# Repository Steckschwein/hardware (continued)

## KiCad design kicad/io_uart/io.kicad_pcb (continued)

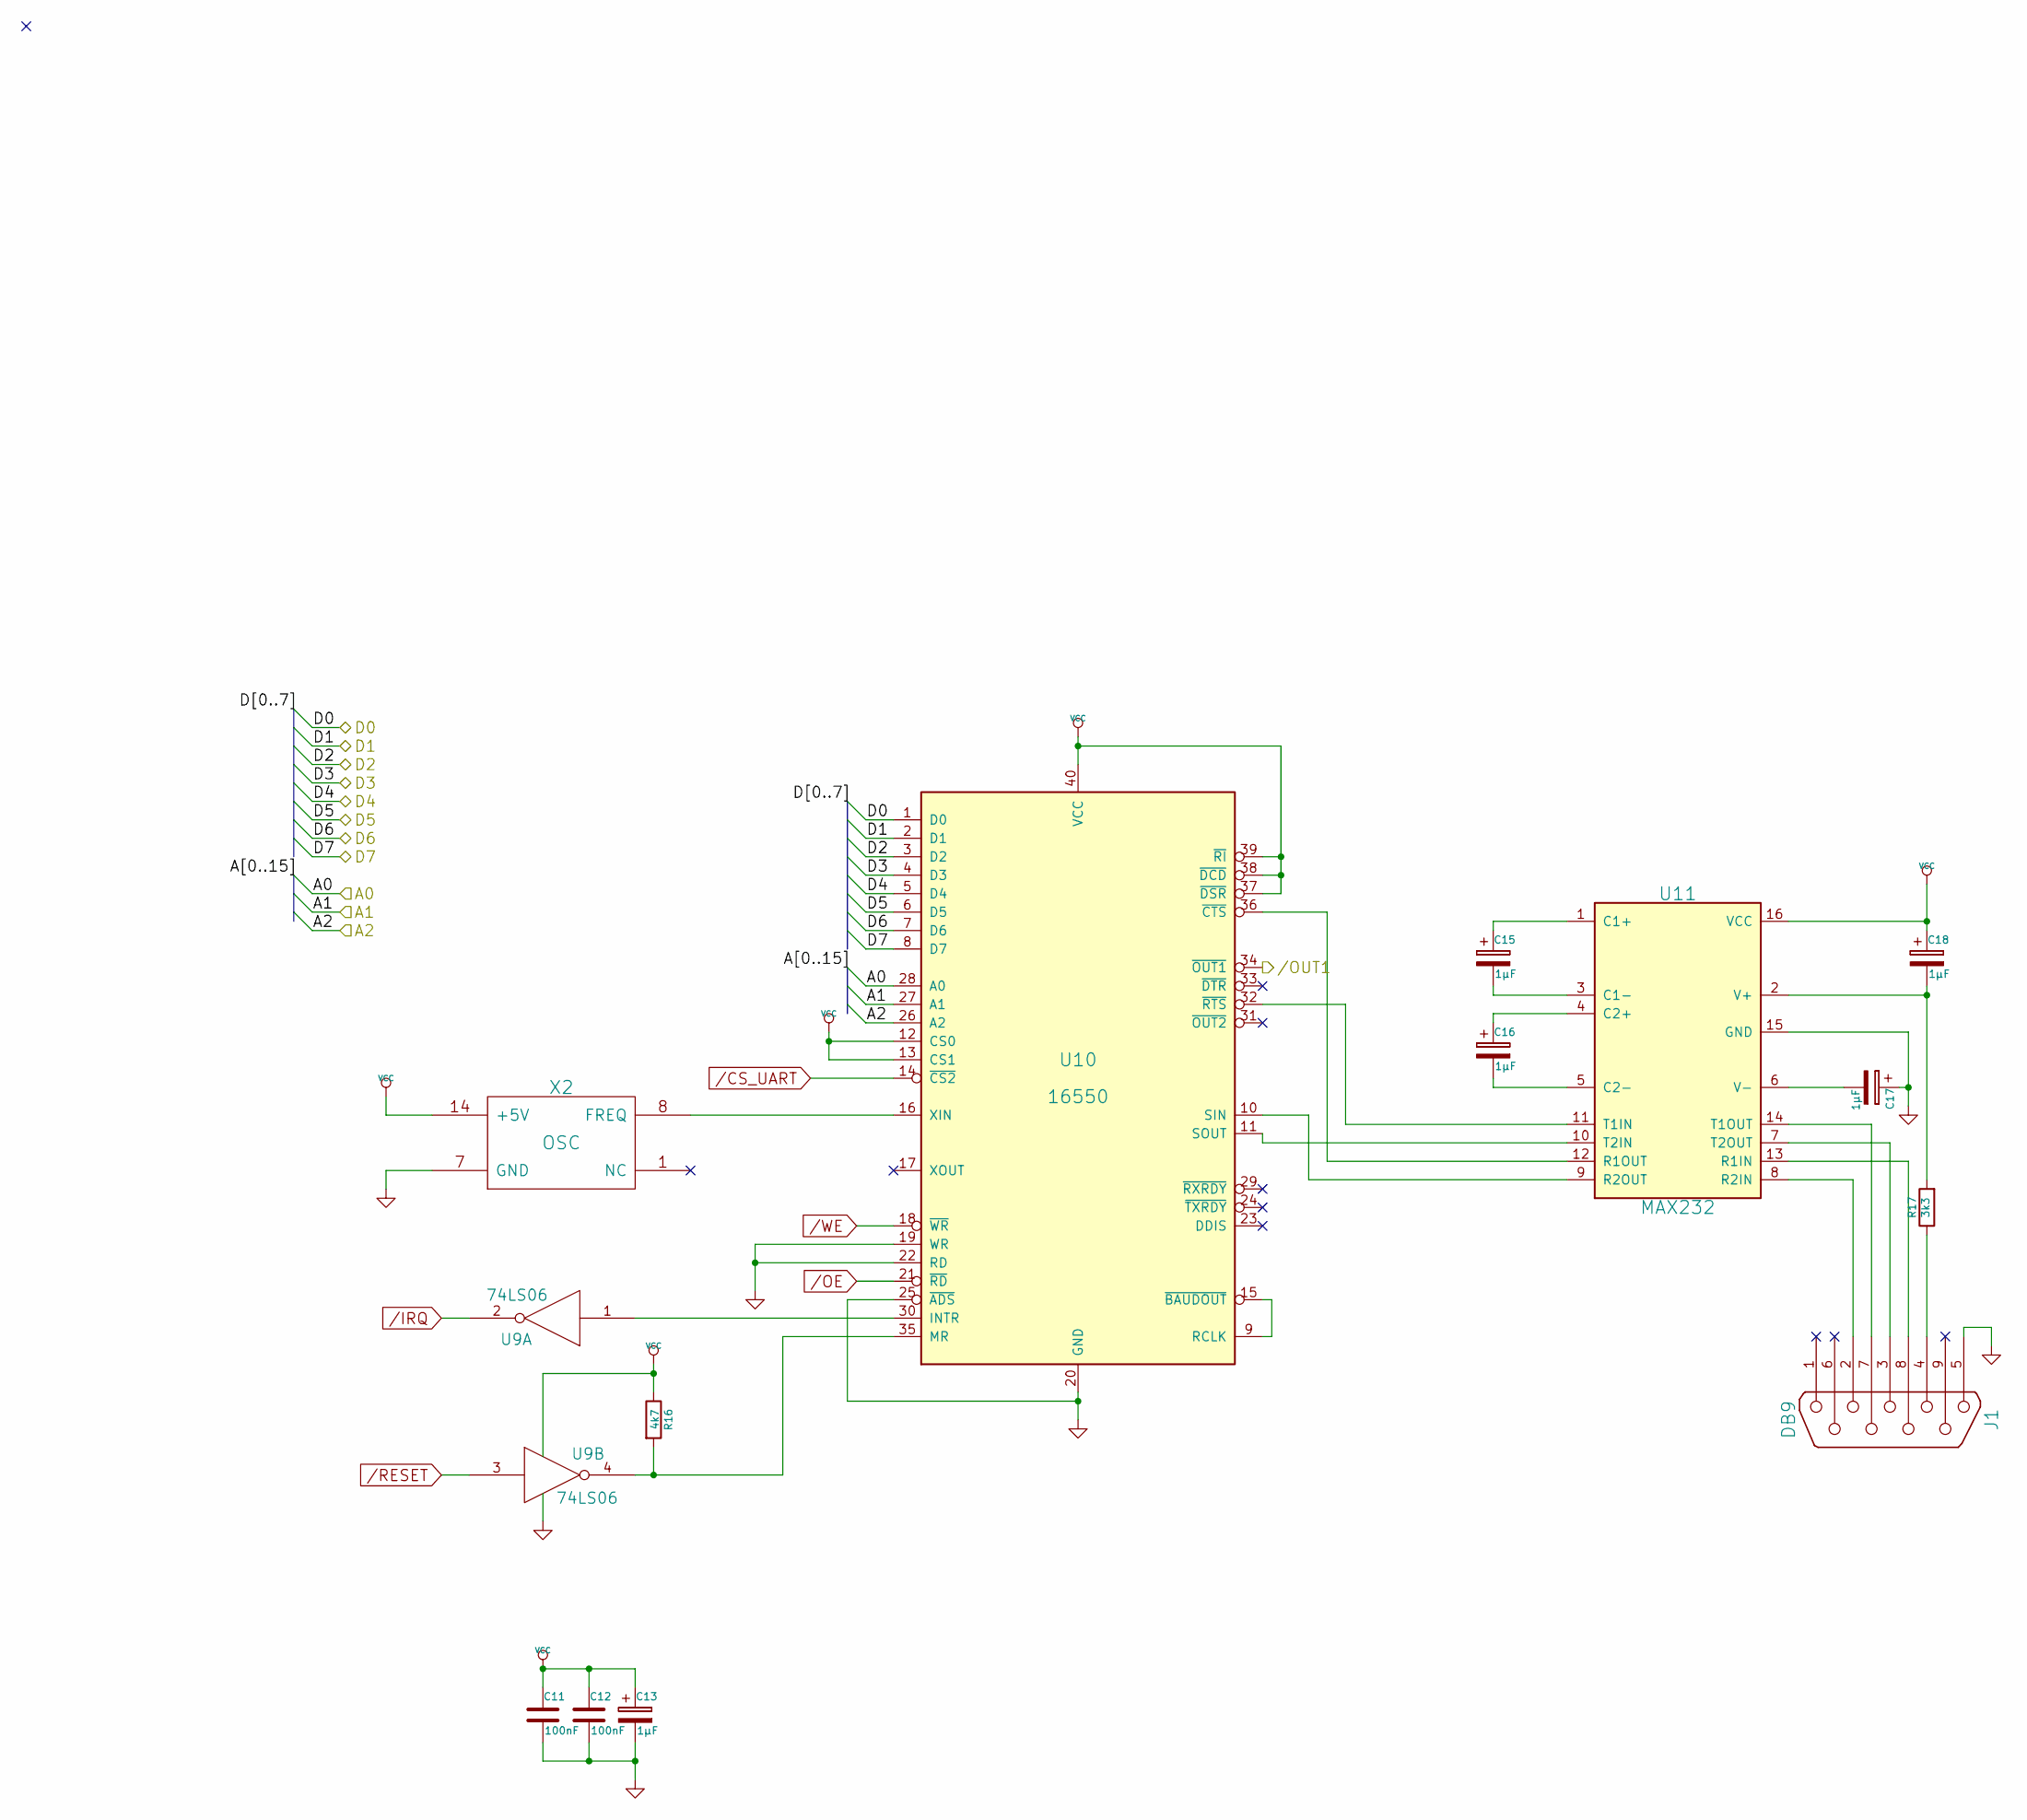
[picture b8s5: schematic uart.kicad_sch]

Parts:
C11, C12: 100nF; C_Rect_L4_W2.5_P2.5
C13, C15, C16, C17, C18: 1µF; C_Radial_D5_L6_P2.5
J1: DB9; DB9MC
R16: 4k7; Resistor_Horizontal_RM7mm
R17: 3k3; Resistor_Horizontal_RM7mm
U9: 74LS06; DIP-14_W7.62mm_LongPads
U10: 16550; DIP-40_W15.24mm_LongPads
U11: MAX232; DIP-16_W7.62mm_LongPads
X2: OSC; KXO-200_LargePads

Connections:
/CS_UART: U10.14 (~CS2); also elsewhere on the board
/Connector/A0: U10.28 (A0); also elsewhere on the board
/Connector/A1: U10.27 (A1); also elsewhere on the board
/Connector/A2: U10.26 (A2); also elsewhere on the board
/Connector/D0: U10.1 (D0); also elsewhere on the board
/Connector/D1: U10.2 (D1); also elsewhere on the board
/Connector/D2: U10.3 (D2); also elsewhere on the board
/Connector/D3: U10.4 (D3); also elsewhere on the board
/Connector/D4: U10.5 (D4); also elsewhere on the board
/Connector/D5: U10.6 (D5); also elsewhere on the board
/Connector/D6: U10.7 (D6); also elsewhere on the board
/Connector/D7: U10.8 (D7); also elsewhere on the board
/IRQ: U9.2; also elsewhere on the board
/Joystick Ports//JOYPORT_ENABLE: U10.34 (~OUT1); also elsewhere on the board
/OE: U10.21 (~RD); also elsewhere on the board
/RESET: U9.3; also elsewhere on the board
/WE: U10.18 (~WR); also elsewhere on the board
GND: C11.2, C12.2, C13.2, C17.1, J1.5, U9.7 (GND), U10.19 (WR), U10.20 (GND), U10.22 (RD), U10.25 (~ADS), U11.15 (GND), X2.7 (GND); also elsewhere on the board
unnamed: C15.1, U11.1 (C1+)
unnamed: C15.2, U11.3 (C1-)
unnamed: C16.1, U11.4 (C2+)
unnamed: C16.2, U11.5 (C2-)
unnamed: C17.2, U11.6 (V-)
unnamed: C18.2, R17.2, U11.2 (V+)
unnamed: J1.2, U11.8 (R2IN)
unnamed: J1.3, U11.7 (T2OUT)
unnamed: J1.4, R17.1
unnamed: J1.7, U11.14 (T1OUT)
unnamed: J1.8, U11.13 (R1IN)
unnamed: R16.2, U9.4, U10.35 (MR)
unnamed: U10.10 (SIN), U11.9 (R2OUT)
unnamed: U10.11 (SOUT), U11.10 (T2IN)
unnamed: U10.9 (RCLK), U10.15 (~BAUDOUT)
unnamed: U10.16 (XIN), X2.8 (FREQ)
unnamed: U9.1, U10.30 (INTR)
unnamed: U10.32 (~RTS), U11.11 (T1IN)
unnamed: U10.36 (~CTS), U11.12 (R1OUT)
VCC: C11.1, C12.1, C13.1, C18.1, R16.1, U9.14 (VCC), U10.12 (CS0), U10.13 (CS1), U10.37 (~DSR), U10.38 (~DCD), U10.39 (~RI), U10.40 (VCC), U11.16 (VCC), X2.14 (+5V); also elsewhere on the board

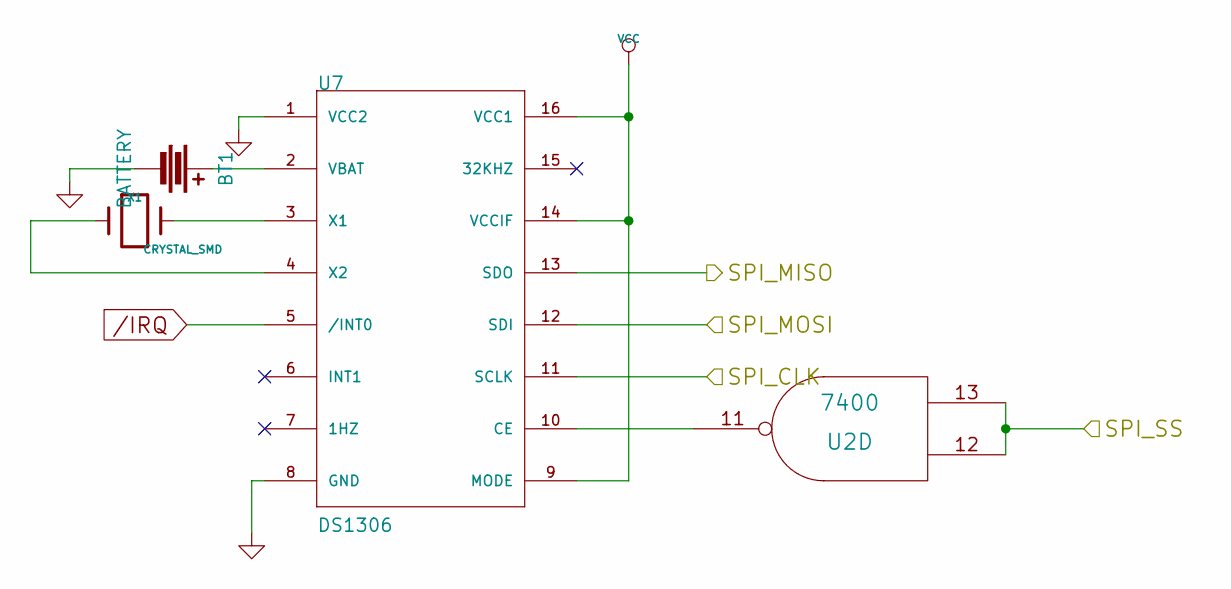
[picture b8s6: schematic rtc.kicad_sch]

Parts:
BT1: BATTERY; CR2032H
U2: 7400; DIP-14_W7.62mm_LongPads
U7: DS1306; DIP-16_W7.62mm_LongPads
X1: CRYSTAL_SMD; Crystal_Round_Vertical_3mm_BigPad

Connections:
/IRQ: U7.5 (/INT0); also elsewhere on the board
/PS/2 Controller/SPI_CLK: U7.11 (SCLK); also elsewhere on the board
/PS/2 Controller/SPI_MISO: U7.13 (SDO); also elsewhere on the board
/PS/2 Controller/SPI_MOSI: U7.12 (SDI); also elsewhere on the board
/RTC/SPI_SS: U2.12, U2.13; also elsewhere on the board
GND: BT1.2, U2.7 (GND), U7.1 (VCC2), U7.8 (GND); also elsewhere on the board
unnamed: BT1.1, U7.2 (VBAT)
unnamed: U2.11, U7.10 (CE)
unnamed: U7.3 (X1), X1.2
unnamed: U7.4 (X2), X1.1
VCC: U2.14 (VCC), U7.9 (MODE), U7.14 (VCCIF), U7.16 (VCC1); also elsewhere on the board

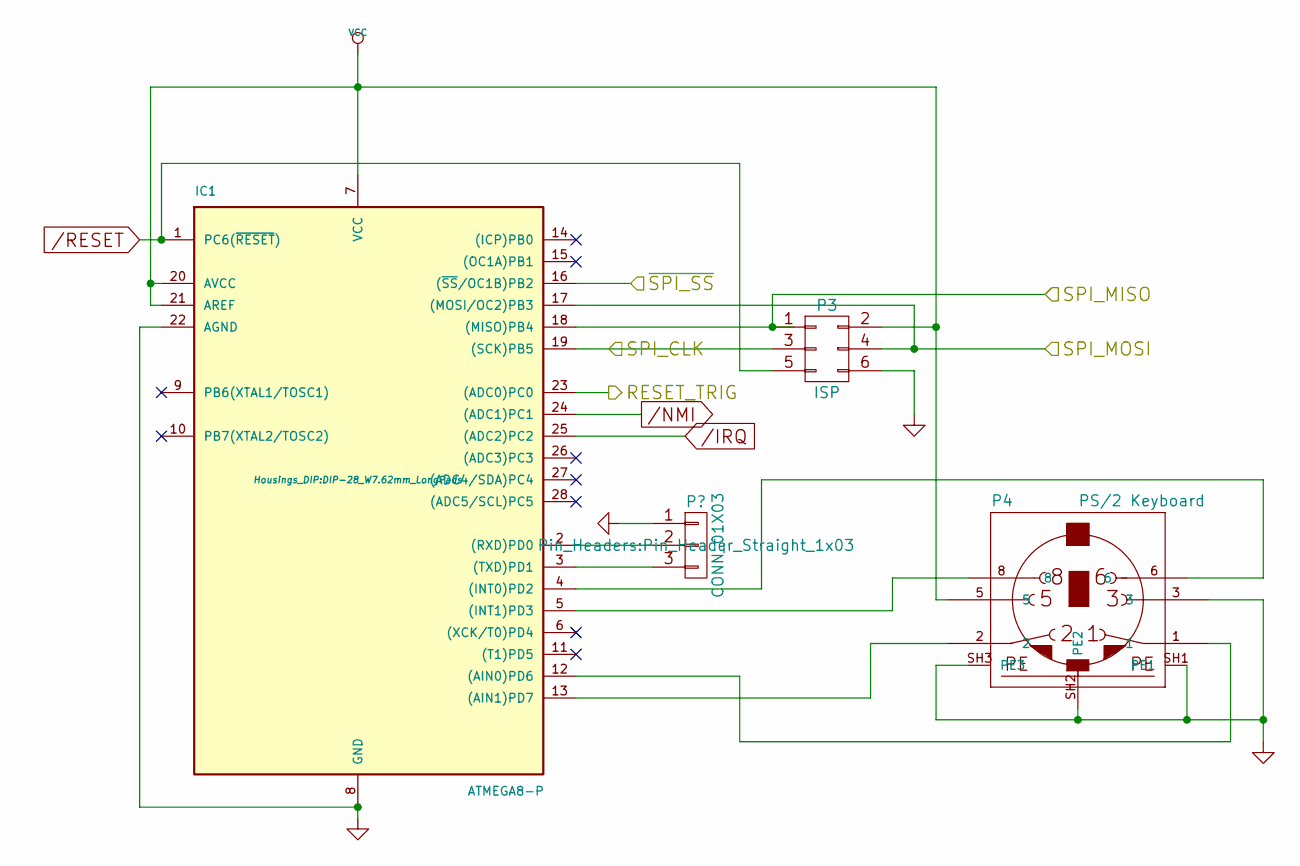
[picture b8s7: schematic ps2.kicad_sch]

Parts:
IC1: ATMEGA8-P; DIP-28_W7.62mm_LongPads
P3: ISP; Pin_Header_Angled_2x03
P4: PS/2 Keyboard; mini_din-M_DIN6

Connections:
/Connector/RESET_TRIG: IC1.23 ((ADC0)PC0); also elsewhere on the board
/IRQ: IC1.25 ((ADC2)PC2); also elsewhere on the board
/NMI: IC1.24 ((ADC1)PC1); also elsewhere on the board
/PS/2 Controller/SPI_CLK: IC1.19 ((SCK)PB5), P3.3; also elsewhere on the board
/PS/2 Controller/SPI_MISO: IC1.18 ((MISO)PB4), P3.1; also elsewhere on the board
/PS/2 Controller/SPI_MOSI: IC1.17 ((MOSI/OC2)PB3), P3.4; also elsewhere on the board
/PS/2 Controller/~SPI_SS: IC1.16 ((~SS/OC1B)PB2); also elsewhere on the board
/RESET: IC1.1 (PC6(~RESET)), P3.5; also elsewhere on the board
GND: IC1.8 (GND), IC1.22 (AGND), P3.6, P4.3, P4.SH1 (PE1), P4.SH2 (PE2), P4.SH3 (PE3); also elsewhere on the board
unnamed 56: IC1.2 ((RXD)PD0); also elsewhere on the board
unnamed 57: IC1.3 ((TXD)PD1); also elsewhere on the board
unnamed: IC1.4 ((INT0)PD2), P4.6
unnamed: IC1.5 ((INT1)PD3), P4.8
unnamed: IC1.12 ((AIN0)PD6), P4.1
unnamed: IC1.13 ((AIN1)PD7), P4.2
VCC: IC1.7 (VCC), IC1.20 (AVCC), IC1.21 (AREF), P3.2, P4.5; also elsewhere on the board

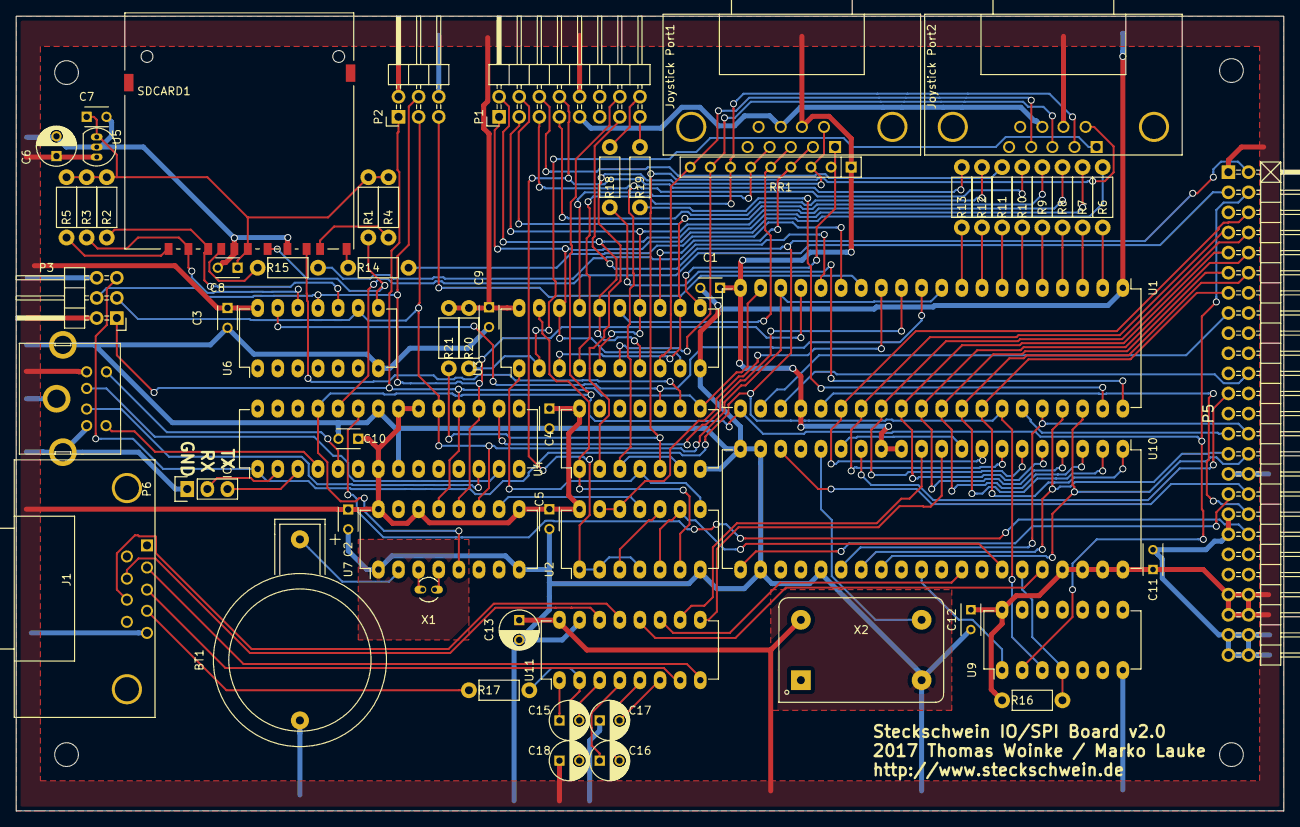
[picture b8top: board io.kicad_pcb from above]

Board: 2 copper layers, 160.0 x 100.3 mm, 67 parts (0 on the bottom side), 105 nets.

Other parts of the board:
Joystick Port1, Joystick Port2: DB9; DB9MC
MH1, MH2, MH3, MH4: MountingHole_3mm_RevA_Date21Jun2010; MountingHole_3mm
P6: CONN_01X03; Pin_Header_Straight_1x03
SDCARD1: SD_Card; SD_Card_Receptacle

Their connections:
/SD Card/SD_CARD_DETECT: SDCARD1.10; also elsewhere on the board
/SD Card/SD_WRITE_PROTECT: SDCARD1.11; also elsewhere on the board
GND: Joystick Port1.8, Joystick Port2.8, P6.1, SDCARD1.3, SDCARD1.6; also elsewhere on the board
unnamed 49: SDCARD1.4; also elsewhere on the board
unnamed 56: P6.2; also elsewhere on the board
unnamed 57: P6.3; also elsewhere on the board
unnamed 89: Joystick Port1.1; also elsewhere on the board
unnamed 90: Joystick Port1.2; also elsewhere on the board
unnamed 91: Joystick Port1.3; also elsewhere on the board
unnamed 92: Joystick Port1.4; also elsewhere on the board
unnamed 94: Joystick Port1.6; also elsewhere on the board
unnamed 96: Joystick Port2.1; also elsewhere on the board
unnamed 97: Joystick Port2.2; also elsewhere on the board
unnamed 98: Joystick Port2.3; also elsewhere on the board
unnamed 99: Joystick Port2.4; also elsewhere on the board
unnamed 101: Joystick Port2.6; also elsewhere on the board
unnamed 103: SDCARD1.5; also elsewhere on the board
unnamed 104: SDCARD1.2; also elsewhere on the board
unnamed 105: SDCARD1.1; also elsewhere on the board
unnamed 106: SDCARD1.8; also elsewhere on the board
unnamed 107: SDCARD1.9; also elsewhere on the board
unnamed 121: SDCARD1.7; also elsewhere on the board
VCC: Joystick Port1.7, Joystick Port2.7; also elsewhere on the board

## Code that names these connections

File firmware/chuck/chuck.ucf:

NET CPU_d<7>      LOC = P62;
NET CPU_d<6>      LOC = P63;
NET CPU_d<5>      LOC = P61;
NET CPU_d<4>      LOC = P58;
NET CPU_d<3>      LOC = P57;
NET CPU_d<2>      LOC = P56;
NET CPU_d<1>      LOC = P55;
NET CPU_d<0>      LOC = P54;
#
NET CPU_a<0>      LOC = P65;
NET CPU_a<1>      LOC = P66;
#
NET CPU_a<4>      LOC = P67;
NET CPU_a<5>      LOC = P68;
NET CPU_a<6>      LOC = P69;
NET CPU_a<7>      LOC = P70;
NET CPU_a<8>      LOC = P71;
NET CPU_a<9>      LOC = P72;
NET CPU_a<10>     LOC = P75;
NET CPU_a<11>     LOC = P76;
NET CPU_a<12>     LOC = P77;
NET CPU_a<13>     LOC = P79;
NET CPU_a<14>     LOC = P80;
NET CPU_a<15>     LOC = P81;
#
NET EXT_a<14>     LOC = P82;
NET EXT_a<15>     LOC = P83;
NET EXT_a<16>     LOC = P84;
NET EXT_a<17>     LOC = P1;
NET EXT_a<18>     LOC = P2;
#
NET CS_OPL   	  LOC = P53;
NET CS_VIA        LOC = P51;
NET CS_SLOT1      LOC = P50;
NET CS_SLOT0      LOC = P39;
NET CSR_VDP       LOC = P47;
NET CSW_VDP       LOC = P25;
NET CS_UART       LOC = P48;
NET CS_ROM        LOC = P4;
NET CS_RAM        LOC = P5;
NET CS_BUFFER     LOC = P52;
#
#
NET CPU_rw    	  LOC = P44; 
NET OE        	  LOC = P6; 
NET WE    	  LOC = P7; 
# NET W		  LOC = P11;
# NET R		  LOC = P26;
NET CPU_phi2      LOC = P3; 
#
NET CPU_rdy       LOC = P40;
NET VDP_wait      LOC = P45;
#
NET CLKIN         LOC = P9; # -- global clock: Pin 9,10,12###
NET RESET         LOC = P74; # -- global reset: Pin 74

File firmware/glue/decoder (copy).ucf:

#PACE: Start of Constraints generated by PACE

#PACE: Start of PACE I/O Pin Assignments
NET "A<0>"  LOC = "P8"  ;
NET "A<10>"  LOC = "P24"  ;
NET "A<11>"  LOC = "P25"  ;
NET "A<1>"  LOC = "P9"  ;
NET "A<2>"  LOC = "P11"  ;
NET "A<3>"  LOC = "P12"  ;
NET "A<4>"  LOC = "P13"  ;
NET "A<5>"  LOC = "P14"  ;
NET "A<6>"  LOC = "P18"  ;
NET "A<7>"  LOC = "P19"  ;
NET "A<8>"  LOC = "P20"  ;
NET "A<9>"  LOC = "P22"  ;
NET "CS_HIRAM"  LOC = "P35"  ;
NET "CS_IO"  LOC = "P44"  ;
NET "CS_LORAM"  LOC = "P34"  ;
NET "CS_ROM"  LOC = "P33"  ;
NET "CS_UART"  LOC = "P36"  ;
NET "CS_VDP"  LOC = "P38"  ;
NET "CS_VIA"  LOC = "P37"  ;
NET "MEMCTL"  LOC = "P43"  ;
NET "PHI2"  LOC = "P5"  ;
NET "RD"  LOC = "P27"  ;
NET "RDY"  LOC = "P29"  ;
NET "ROMOFF"  LOC = "P1"  ;
NET "RW"  LOC = "P26"  ;
NET "WR"  LOC = "P28"  ;

#PACE: Start of PACE Area Constraints

#PACE: Start of PACE Prohibit Constraints

#PACE: End of Constraints generated by PACE

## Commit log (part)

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2019-03-11 add serial debug
2019-03-11 enable spi slave
2019-03-11 optimized scancode decoding
2019-03-13 cleanup
2019-03-13 cleanup fillers
2019-03-13 enable serial debug via define
2019-03-26 serial headers
2019-03-30 skkdfnskj
2019-04-07 send mode (unusable, bug ridden, incomplete, still sends crap)
2019-04-07 still buggy
2019-04-07 still broken
2019-04-07 k,hdc
2019-04-10 remove avrdude device specifics, dependency fix
2019-05-01 decoder/wsgen/clock cpld vhdl sources
2019-05-04 tests, asserts and fixes
2019-05-04 full address decoder test broken for no apparent reason
2019-05-04 new project, test, fixes
2019-05-04 vhd files back
2019-05-05 reset line, test waveform config
2019-05-05 impact project file
2019-05-08 rdy generation, clock generation PHI2 = CLKIN /2 (saves space)
2019-05-14 fixes
2019-05-27 C16 value
2019-06-12 cpu_mem_rdy.csv cleanup, suppliers
2019-06-12 suggest different rams
2019-07-04 README created online with Bitbucket
2019-07-28 plcc84, full address bus, latch
2019-07-29 removed freq divider
2019-07-29 very cheap cs_ram solution
2019-07-29 almost
2019-07-30 cs_ram cheap solution, rev. 2
2019-08-03 register writes use cs_IOnn lines for debug output
2019-08-03 fix cs_ram, test register write to romoff
2019-08-03 register writes, a13/a14 mapping for rom accesses code reorg removed cs_io03
2019-08-03 cpu pins: vp, sync, be
2019-08-05 pin names, irq and nmi lines
2020-05-30 new address decoder inital
2020-05-31 fixes, testbench
2020-09-27 +keboard, send commands
2020-09-27 +update
2020-09-28 +send keyboard codes
2020-09-29 +keyboard util
2020-09-29 +merge
2020-09-29 +fix makefile
2020-09-29 +fix caps lock / shift
2020-09-29 +recv. keyboard commands
2020-10-03 +kbd status support +improved cmd handling
2020-10-04 fix shift key
2020-10-04 if proper formatted
2020-10-05 assert IRQ when byte in buffer, release when byte reansferred via spi
2020-10-05 +cmd timeout +doc
2020-10-07 +status check
2020-10-10 +echo watchdog +fix timing on identify
2020-10-11 pull irq line when buffer >0 bytes, release irq when buffer empty
2020-11-09 use IRQ by default
2020-11-14 +reset and init sequence +clean code
2020-11-19 removed xilinx projects
2020-12-31 +revision keyboard firmware and host irq handling
2021-01-03 +kbd cmd engine +bios init sequence
2021-05-27 cpu_mem_cpld initial
2021-08-22 gitignore file
2021-08-29 io components
2022-03-03 cpld version with uart
2022-03-03 libs
2022-03-03 remove all global labels
2022-04-24 initial
2022-04-24 add more stuff
2022-04-24 nope
2022-04-24 remove csw_vdp, csr_vdp. add cs_vdp_
2022-04-24 removed csr_vdp, csw_vdp. cs_vdp only
2022-04-24 pinout rearranged for better fitting
2022-04-24 csw_vdp, csr_vdp replaced by cs_vdp, cleanup
2022-04-24 more tests
2022-04-26 use fitter generated pinout
2022-05-16 cpu cpld 512
2022-05-18 add cs_uart2, remove a2,a3
2022-05-18 added cs_uart2, /WE for EEPROM
2022-05-18 uart2 pin assignment
2022-05-18 extra capacitor, revision text
2022-05-18 eeprom rw jumper
2022-05-20 new routing attempt
2022-05-22 cleanup autorouted traces
2022-05-22 zones refilled
2022-05-22 gerber files
2022-05-25 swap uart and uart2
2022-08-25 rdygen disabled
2022-09-04 data bus interface back on
2022-09-10 test with hardcoded cs_rom and cs_ram
2022-09-20 rdwr process
2022-09-23 +ROM read ok
2022-09-24 +with uart
2022-09-26 io select term long form
2022-09-26 uart2 cs decoding long form
2022-09-26 reg_select decoding long form
2022-09-26 +concurrent mode
2022-09-26 cs terms longform
2022-09-29 +clean code
2022-09-29 +bitmask conditionals
2022-10-01 +bios ram,rom,uart OK +clean code
2022-10-02 +xmodem cpld bios +clean vhdl
2022-10-03 +static ctrl port read
2022-10-03 +register read
2022-10-04 +init and reg read ok
2022-10-04 +ascii out
2022-10-04 +reg write nearly
2022-10-04 +reg read/write OK :)
2022-10-04 +ext ram +memtest
2022-10-05 +improved memtest
2022-10-05 fix missing cs vdp
2022-10-05 +wait states on cs_rom +revision bank test
2022-10-05 +tristate rdy by default
2022-10-05 +revision rdy, 8Mhz ok
2022-10-07 +clean
2022-10-08 +fix rdy timing +add vdp, opl cs
2022-10-08 +16Mhz ok
2022-10-09 +bios, kernel, timing
2022-10-20 cs_buffer (U10)
2022-10-20 cs buffer to pin 62
2022-10-21 pin 75 even better
2022-10-21 cs line for data bus buffer
2022-10-21 removed sbc
2023-01-15 sbc core
2023-02-06 fix cs_buffer generation
2023-02-11 +memcheck ram/rom bios
2023-02-26 audio video stuff, new placement
2023-03-01 ref #52 +revision, clean code +disable keyboard irq
2023-03-22 pinout for sbc, removed UART2 CS
2023-03-22 cs slot0/slot1
2023-03-22 pinout adjustments
2023-03-22 cpld pinout
2023-03-22 more vias to gnd
2023-03-28 din connector footprints
2023-03-28 complete schematics
2023-03-29 io area relayout
2023-04-01 pinout expansion slot
2023-04-01 added CSR_VDP, CSW_VDP, W, R
2023-04-01 removed U17
2023-04-01 io area placement
2023-04-03 fix ERC messages
2023-04-04 cleanup ERC warnings and errors
2023-04-04 erc cleanup
2023-04-07 routing
2023-04-07 more routing
2023-04-07 routing..
2023-04-10 DRC hell
2023-04-11 DRC hell II
2023-04-11 vdp xtal capacitor footprints THT
2023-04-11 fix CS_OPL, fix DRC warnings
2023-04-11 DRC warnings
2023-04-12 added magic irq diode for W65c22S
2023-04-12 regular sd socket separate masses for analog and digital cleanup routing
2023-04-12 swap pins d6 d7
2023-04-12 created gerber files
2023-04-30 fix mixup of vcc and gnd at the 74244
2023-04-30 fix mixup of vcc and gnd on U29
2023-04-30 fix ISE latch warnings
2023-05-02 backups exclude
2023-05-02 moved .gitignore to kicad/
2023-05-07 filter
2023-05-10 connect cpu_r/W to CPLD
2023-05-10 fix CS_OPL pin mixup
2023-05-10 fix cpu_r/w connection to CPLD
2023-05-11 added R and W, cleanup
2023-05-14 fix dimensions
2023-05-14 fix some ugly routin
2023-05-17 new ps/2 mini din footprint
2023-05-17 better s-video jack footprint
2023-05-24 resistor footprints
2023-06-01 dip 28 footprint
2023-06-05 fix DRC warnings
2023-06-17 +rollback d_out - tbd.
2023-06-19 moved all symbols into custom library
2023-06-20 moved all footprints into local library
2023-06-20 removed all other project libraries
2023-07-01 generate phi2 from master clock via counter TEST: gate cs_uart, csw_vdp, csr_vdp via PHI2
2023-07-02 fix spi selects
2023-07-02 fix sd card socket symbol
2023-07-02 assigned footprint
2023-07-02 cosmetics
2023-07-02 sd card detect back
2023-07-02 fix drc error
2023-07-02 sd card detect routed, cosmetics
2023-07-02 sd card pullup resistor pack
2023-07-02 revision text
2023-07-02 +sbc r0.1 1Mhz - vdp ok
2023-07-02 renamed SPI_SSn to SPI_SS_SDCARD, etc
2023-07-03 update layout with new spi ss signal names
2023-07-03 make ISP connector more accessible, minor routing fixes
2023-07-05 +fix R/W +generic timing
2023-07-05 +spec.
2023-07-06 +fix calc
2023-07-09 +fmt
2023-07-10 +combined r/w
2023-07-10 cleanup silkscreen warnings
2023-07-10 new gerbers v.04
2023-07-12 removed no connect from slot1
2023-07-16 +8Mhz +ws/rdy for opl, vdp, rom
2023-07-17 stuff
2023-07-17 +rdy Z output
2023-07-18 +simplify logic, single /OE,/WE
2023-07-19 separate 500 ohm pullup for CPU_RDY
2023-07-19 removed /R and /W, connected /BUF_OE and /BUF_WR to OPL instead
2023-07-19 beauty fixes
2023-07-19 font sizes
2023-07-19 footprint identifiers invisible
2023-07-19 fix ERC errors
2023-07-19 routed OPL2 /RD /WR, new RDY pullup
2023-07-19 fixed board revision
2023-07-20 v5.0 gerbers
2023-07-26 component values/units cleanup
2023-07-27 label font sizes
2023-07-28 audio jack, usb jack, reset button positions, cosmetic changes
2023-07-30 gerbers v.06
2023-07-30 v 0.6 gerbers
2023-07-30 fix gitignore
2023-09-24 atmega168 +initial
2023-10-15 + +1ws
2024-03-06 spi65 initial
2024-05-02 sbc cpld (#1)
    * +fix R/W
    +generic timing
    * +spec.
    * +fix calc
    * +fmt
    * +combined r/w
2024-05-02 enable wait states for expansion slots
2024-05-08 SPI65/B initial
2024-05-08 phi2 polarity
2024-09-12 plcc32 flash adapter
2024-09-22 +clean code +rom cs clocked
2024-09-25 clock WE line instead of CS_RAM get rid of R and W
2024-09-25 qualify /OE through CLK, too
2025-02-10 +feat: write protext bit (draft)
2025-02-11 +feat: clean
2025-04-08 Add README.md
2025-05-06 makefile and build files
2025-05-07 gitignore
2025-05-07 removed clock divider
2025-05-07 6 ws
2025-05-08 message
2025-05-11 rdy not tri state anymore, separate input for vdp wait
2025-05-12 4 bit ws count
2025-05-12 no ws for UART
2025-05-12 slew rate fast (test)
